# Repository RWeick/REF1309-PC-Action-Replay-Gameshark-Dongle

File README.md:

# REF1309-PC-Action-Replay-Gameshark-Dongle
The kicad schematic, PCB file, and PIC Microcontroller dump of the PC Action Replay / Gameshark Dongle for use with Win95/98

Everything necessary to produce the security dongle for the Win 95/98 PC Gameshark and Action Replay software. Details on the functionality of the PIC12C508A can be found [here.](https://github.com/parasyte/picard) Though that page discusses the PS1 Gameshark Pro 12C508A, the code used on both PICs is nearly identical. There are small differences not tied to operation. This wouldn't have been possible without [Nes-player4Life](https://github.com/Nes-player4Life) who bravely subjected his PC Gameshark Dongle to science in order for this to exist, and [Parasyte](https://github.com/parasyte) who meticulously reverse engineered the function of the PIC12C508A available at the above link.

The parallel port connectors are arranged as such: from the orientation of the image shown, the male connector is on the left, and the female is on the right. 

This dongle is identical to the [PC Gameshark Dongle](https://github.com/RWeick/PC-Gameshark-Dongle) I had previously reverse engineered here, with the exception that Datel had updated the PCB layout. All of the components, values, and code is otherwise the same.

PCB Thickness: 1.2 mm

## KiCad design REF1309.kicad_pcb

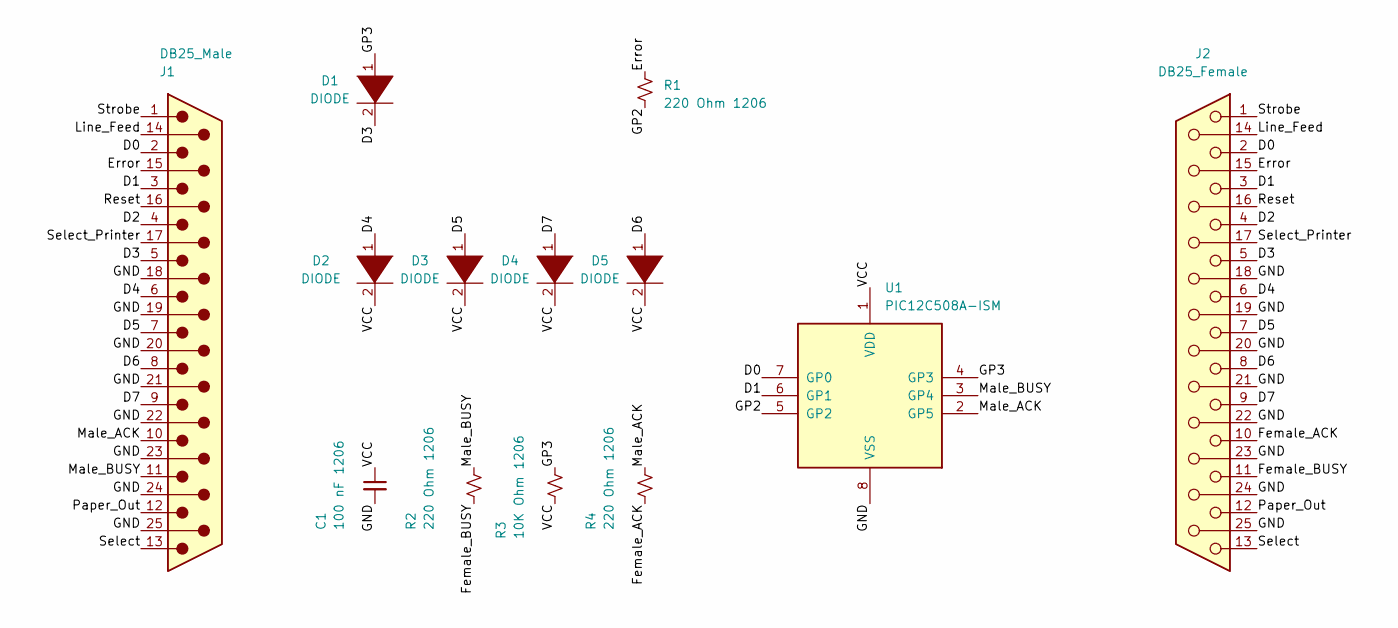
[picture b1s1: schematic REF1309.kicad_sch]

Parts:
C1: 100 nF 1206; Cap or Res
D1, D2, D3, D4, D5: DIODE; Diode
J1: DB25_Male; DSUB-25_Male_EdgeMount_P2.77mm
J2: DB25_Female; DSUB-25_Female_EdgeMount_P2.77mm
R1, R2, R4: 220 Ohm 1206; Cap or Res
R3: 10K Ohm 1206; Cap or Res
U1: PIC12C508A-ISM; PIC 12C508A

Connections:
/D0: J1.2, J2.2, U1.7 (GP0)
/D1: J1.3, J2.3, U1.6 (GP1)
/D2: J1.4, J2.4
/D3: D1.2 (A), J1.5, J2.5
/D4: D2.1 (K), J1.6, J2.6
/D5: D3.1 (K), J1.7, J2.7
/D6: D5.1 (K), J1.8, J2.8
/D7: D4.1 (K), J1.9, J2.9
/Error: J1.15, J2.15, R1.1
/Female_ACK: J2.10, R4.2
/Female_BUSY: J2.11, R2.2
/GND: C1.2, J1.18, J1.19, J1.20, J1.21, J1.22, J1.23, J1.24, J1.25, J2.18, J2.19, J2.20, J2.21, J2.22, J2.23, J2.24, J2.25, U1.8 (VSS)
/GP2: R1.2, U1.5 (GP2)
/GP3: D1.1 (K), R3.1, U1.4 (GP3)
/Line_Feed: J1.14, J2.14
/Male_ACK: J1.10, R4.1, U1.2 (GP5)
/Male_BUSY: J1.11, R2.1, U1.3 (GP4)
/Paper_Out: J1.12, J2.12
/Reset: J1.16, J2.16
/Select: J1.13, J2.13
/Select_Printer: J1.17, J2.17
/Strobe: J1.1, J2.1
/VCC: C1.1, D2.2 (A), D3.2 (A), D4.2 (A), D5.2 (A), R3.2, U1.1 (VDD)

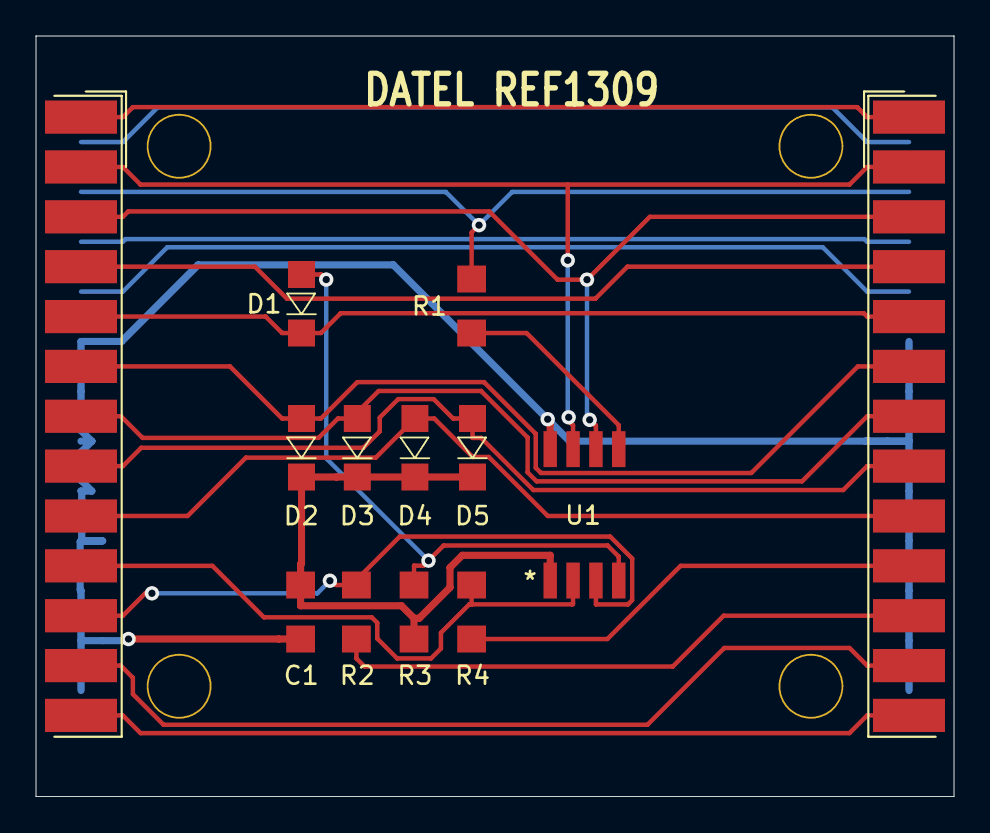
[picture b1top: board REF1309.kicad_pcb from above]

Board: 2 copper layers, 51.0 x 42.2 mm, 19 parts (0 on the bottom side), 23 nets.

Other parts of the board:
DMark1, DMark2, DMark3, DMark4, DMark5: dcff1695-539e-442e-afee-9485378ce13a
Holes: Drill Holes
